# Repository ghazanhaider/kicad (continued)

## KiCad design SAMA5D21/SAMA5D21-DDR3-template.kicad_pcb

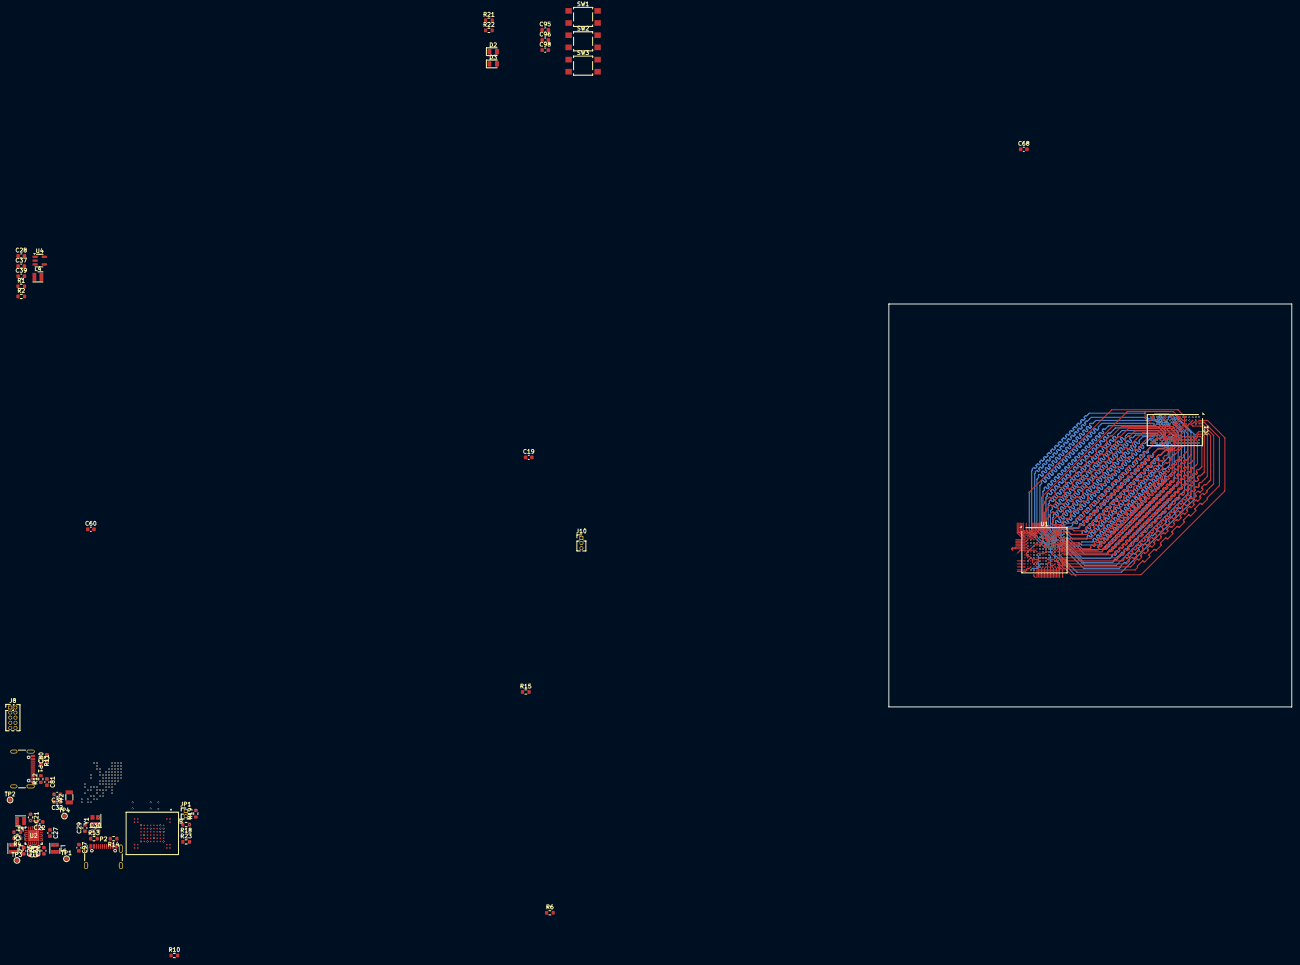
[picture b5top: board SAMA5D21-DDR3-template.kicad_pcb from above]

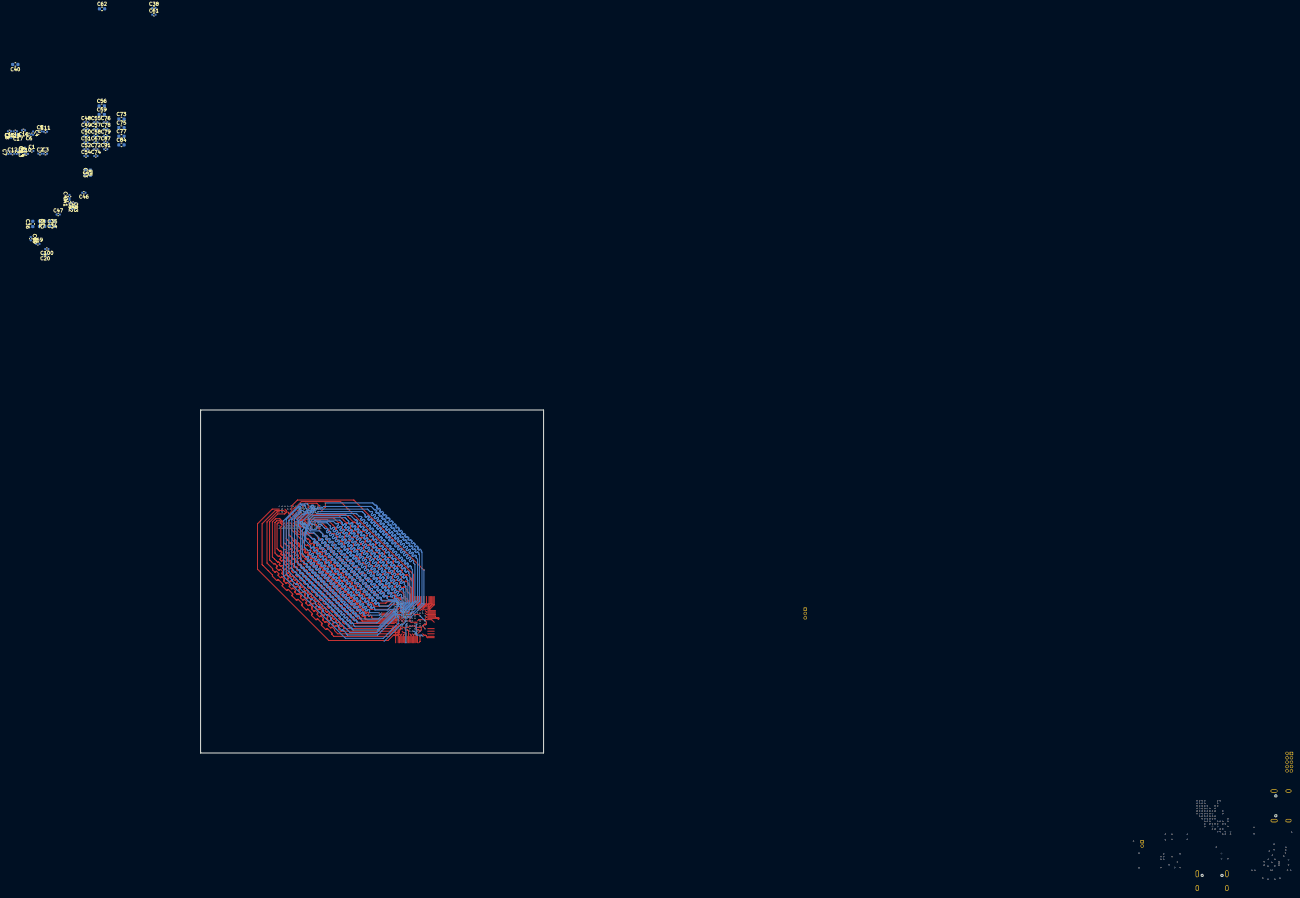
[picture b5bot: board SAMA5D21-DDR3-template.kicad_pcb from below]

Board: 4 copper layers, 127 parts (63 on the bottom side), 104 nets.

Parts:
C1, C2, C3, C4, C5, C6, C7, C8, C9, C10, C11, C12, C13, C14, C15, C16, C17, C18, C20, C38, C41, C42, C43, C44, C45, C46, C47, C48, C49, C50, C51, C52, C54, C55, C57, C58, C61, C67, C69, C72, C74, C76, C78, C79, C87, C91, C99, C100: 100nF; C_0402_1005Metric
C19, C37, C56, C59, C62, C68, C73, C75, C77, C84: 1uF; C_0603_1608Metric
C21, C23, C24: 22uF; C_0603_1608Metric
C22, C25, C26, C27, C28, C36, C39, C80, C81, C97: 4.7uF; C_0603_1608Metric
C29, C30, C31, C32: 16pF; C_0603_1608Metric
C33: 22pF; C_0603_1608Metric
C34, C35, C40, C95, C96, C98: 100nF; C_0603_1608Metric
C60: 10nF; C_0603_1608Metric
D2: LED; LED_0805_2012Metric
D3: PWR; LED_0805_2012Metric
IC1: D1216ECMDXGJD-U; Micron_FBGA-96_7.5x13.5mm_Layout9x16_P0.8mm
J8: SWD; PinHeader_2x05_P1.27mm_Vertical
J10: UART0; PinHeader_1x03_P1.27mm_Vertical
JP1: BOOT; PinHeader_1x02_P1.27mm_Vertical
L1, L2, L3: 2.2uH; L_Wurth_WE-LQSH-2512
L4: 10uH; L_Wurth_WE-LQSH-2512
P1: USB_PWR; USB_C_Receptacle_GCT_USB4105-xx-A_16P_TopMnt_Horizontal
P2: USB-B; USB_C_Receptacle_GCT_USB4105-xx-A_16P_TopMnt_Horizontal
R1: 92.82k; R_0603_1608Metric
R2: 5.1; R_0603_1608Metric
R3, R4, R6: 100k; R_0603_1608Metric
R5: 23.2k 1%; R_0603_1608Metric
R7, R8: 6.8k 1%; R_0603_1608Metric
R10: 240R 1%; R_0603_1608Metric
R11, R12: 5.1k 1%; R_0603_1608Metric
R13, R14: 56k 1%; R_0603_1608Metric
R15: 5.62k 1%; R_0603_1608Metric
R18, R19: 470k; R_0603_1608Metric
R21, R22, R23: 1k; R_0603_1608Metric
SW1: BUTTON; SW_SPST_TL3305A
SW2: START; SW_SPST_TL3305A
SW3: RESET; SW_SPST_TL3305A
TP1: VBUS; TestPoint_Pad_D1.0mm
TP2: 3.3V; TestPoint_Pad_D1.0mm
TP3: 1.35V; TestPoint_Pad_D1.0mm
TP4: 1.25V; TestPoint_Pad_D1.0mm
U1: ATSAMA5D21; Microchip_TFBGA-196_11x11mm_Layout14x14_P0.75mm_SMD
U2: PMIC; VQFN24_RMB_MCH
U3: MT29F4G08ABAFAH4-IT:F; BGA63C80P10X12_1050X1300X100N
U4: AP3012; SOT-23-5
Y1: 12MHz; Crystal_SMD_2520-4Pin_2.5x2.0mm
Y2: 32.768kHz; Crystal_SMD_3215-2Pin_3.2x1.5mm

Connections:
+1V25: C24.2, C38.2, C48.1, C49.1, C50.1, C51.1, C52.1, C62.2, C72.1, C73.1, C84.1, L3.1, TP4.1, U1.E8 (VDDCORE), U1.G8 (VDDCORE), U1.H8 (VDDCORE), U1.H9 (VDDCORE), U1.J5 (VDDCORE), U1.M7 (VDDUTMIC), U1.P3 (VDDPLLA), U2.13 (OUT3)
+1V35: C1.2, C2.2, C3.2, C4.2, C5.2, C6.2, C7.2, C8.2, C9.2, C10.2, C11.2, C12.2, C13.2, C14.2, C15.2, C16.2, C17.2, C18.2, C19.2, C23.1, C35.2, C36.1, C41.1, C42.1, C43.1, C44.1, C45.1, C46.1, C47.1, C60.1, C68.1, IC1.A1 (VDDQ_1), IC1.A8 (VDDQ_2), IC1.B2 (VDD_1), IC1.C1 (VDDQ_3), IC1.C9 (VDDQ_4), IC1.D2 (VDDQ_5), IC1.D9 (VDD_2), IC1.E9 (VDDQ_6), IC1.F1 (VDDQ_7), IC1.G7 (VDD_3), IC1.H2 (VDDQ_8), IC1.H9 (VDDQ_9), IC1.K2 (VDD_4), IC1.K8 (VDD_5), IC1.N1 (VDD_6), IC1.N9 (VDD_7), IC1.R1 (VDD_8), IC1.R9 (VDD_9), L2.1, R6.2, R8.1, TP3.1, U1.C6 (VDDIODDR), U1.E10 (VDDIODDR), U1.E12 (VDDIODDR), U1.G10 (VDDIODDR), U1.G12 (VDDIODDR), U1.H11 (VDDIODDR), U1.J10 (VDDIODDR), U2.6 (OUT2)
/DDR3/A0: IC1.N3 (A0), U1.E11 (DDR_A0)
/DDR3/A1: IC1.P7 (A1), U1.C11 (DDR_A1)
/DDR3/A2: IC1.P3 (A2), U1.B12 (DDR_A2)
/DDR3/A3: IC1.N2 (A3), U1.A12 (DDR_A3)
/DDR3/A4: IC1.P8 (A4), U1.D11 (DDR_A4)
/DDR3/A5: IC1.P2 (A5), U1.D14 (DDR_A5)
/DDR3/A6: IC1.R8 (A6), U1.B14 (DDR_A6)
/DDR3/A7: IC1.R2 (A7), U1.D9 (DDR_A7)
/DDR3/A8: IC1.T8 (A8), U1.C10 (DDR_A8)
/DDR3/A9: IC1.R3 (A9), U1.D10 (DDR_A9)
/DDR3/A10/AP: IC1.L7 (A10/AP), U1.F9 (DDR_A10)
/DDR3/A11: IC1.R7 (A11), U1.A11 (DDR_A11)
/DDR3/A12/BC#: IC1.N7 (A12/BC#), U1.B11 (DDR_A12)
/DDR3/A13: IC1.T3 (A13), U1.E13 (DDR_A13)
/DDR3/BA0: IC1.M2 (BA0), U1.F13 (DDR_BA0)
/DDR3/BA1: IC1.N8 (BA1), U1.G13 (DDR_BA1)
/DDR3/BA2: IC1.M3 (BA2), U1.F14 (DDR_BA2)
/DDR3/CAS#: IC1.K3 (CAS#), U1.C13 (DDR_CAS)
/DDR3/CK: IC1.J7 (CK), U1.A13 (DDR_CLK)
/DDR3/CK#: IC1.K7 (CK#), U1.B13 (DDR_CLKN)
/DDR3/CKE: IC1.K9 (CKE), U1.E14 (DDR_CKE)
/DDR3/CS#: IC1.L2 (CS#), U1.F11 (DDR_CS)
/DDR3/DDR_VREF: C34.2, C35.1, C40.1, IC1.H1 (VREFDQ), IC1.M8 (VREFCA), R7.1, R8.2, U1.C12 (DDR_VREF), U1.H12 (DDR_VREF)
/DDR3/DML: IC1.E7 (DML), U1.D8 (DDR_DQM0)
/DDR3/DMU: IC1.D3 (DMU), U1.G14 (DDR_DQM1)
/DDR3/DQL0: IC1.E3 (DQL0), U1.A9 (DDR_D4)
/DDR3/DQL1: IC1.F7 (DQL1), U1.B9 (DDR_D3)
/DDR3/DQL2: IC1.F2 (DQL2), U1.C8 (DDR_D2)
/DDR3/DQL3: IC1.F8 (DQL3), U1.C9 (DDR_D5)
/DDR3/DQL4: IC1.H3 (DQL4), U1.B7 (DDR_D0)
/DDR3/DQL5: IC1.H8 (DQL5), U1.B10 (DDR_D7)
/DDR3/DQL6: IC1.G2 (DQL6), U1.A7 (DDR_D1)
/DDR3/DQL7: IC1.H7 (DQL7), U1.A10 (DDR_D6)
/DDR3/DQSL: IC1.F3 (DQSL), U1.B8 (DDR_DQS0)
/DDR3/DQSL#: IC1.G3 (DQSL#), U1.A8 (DDR_DQSN0)
/DDR3/DQSU: IC1.C7 (DQSU), U1.K14 (DDR_DQS1)
/DDR3/DQSU#: IC1.B7 (DQSU#), U1.K13 (DDR_DQSN1)
/DDR3/DQU0: IC1.D7 (DQU0), U1.H13 (DDR_D8)
/DDR3/DQU1: IC1.C3 (DQU1), U1.L13 (DDR_D12)
/DDR3/DQU2: IC1.C8 (DQU2), U1.H14 (DDR_D9)
/DDR3/DQU3: IC1.C2 (DQU3), U1.L14 (DDR_D13)
/DDR3/DQU4: IC1.A7 (DQU4), U1.J14 (DDR_D11)
/DDR3/DQU5: IC1.A2 (DQU5), U1.K12 (DDR_D15)
/DDR3/DQU6: IC1.B8 (DQU6), U1.J13 (DDR_D10)
/DDR3/DQU7: IC1.A3 (DQU7), U1.J12 (DDR_D14)
/DDR3/RAS#: IC1.J3 (RAS#), U1.C14 (DDR_RAS)
/DDR3/WE#: IC1.L3 (WE#), U1.A14 (DDR_WE)
/DDR3/~DDR_RESET: IC1.T2 (RESET#), R6.1, U1.D13 (~DDR_RESET)
/NAND/NAND_CE: JP1.2 (B), R19.1, U3.C6 (CE#)
/Power/SHDN: U1.N1 (SHDN), U2.3 (PWRHLD)
/Power/START: C95.1, SW2.2, U2.14 (nSTRT)
/Power/WKUP: R4.1, U1.P1 (WKUP), U2.5 (nSTRTO)
/USB/VBG: R15.2, U1.L7 (VBG)
GNDADIOPLL: C1.1, C2.1, C3.1, C4.1, C5.1, C6.1, C7.1, C8.1, C9.1, C10.1, C11.1, C12.1, C13.1, C14.1, C15.1, C16.1, C17.1, C18.1, C19.1, C20.1, C21.2, C22.2, C23.2, C24.1, C25.2, C26.1, C27.2, C28.1, C29.1, C30.1, C31.2, C32.2, C33.2, C34.1, C36.2, C37.2, C38.1, C39.2, C40.2, C41.2, C42.2, C43.2, C44.2, C45.2, C46.2, C47.2, C48.2, C49.2, C50.2, C51.2, C52.2, C54.2, C55.2, C56.2, C57.2, C58.2, C59.2, C60.2, C61.1, C62.1, C67.1, C68.2, C69.1, C72.2, C73.2, C74.2, C75.2, C76.2, C77.2, C78.2, C79.2, C80.2, C81.2, C84.2, C87.2, C91.1, C95.2, C96.2, C97.2, C98.2, C99.1, C100.1, D3.1 (K), IC1.A9 (VSS_1), IC1.B1 (VSSQ_1), IC1.B3 (VSS_2), IC1.B9 (VSSQ_2), IC1.D1 (VSSQ_3), IC1.D8 (VSSQ_4), IC1.E1 (VSS_3), IC1.E2 (VSSQ_5), IC1.E8 (VSSQ_6), IC1.F9 (VSSQ_7), IC1.G1 (VSSQ_8), IC1.G8 (VSS_4), IC1.G9 (VSSQ_9), IC1.J2 (VSS_5), IC1.J8 (VSS_6), IC1.K1 (ODT), IC1.M1 (VSS_7), IC1.M9 (VSS_8), IC1.P1 (VSS_9), IC1.P9 (VSS_10), IC1.T1 (VSS_11), IC1.T9 (VSS_12), J8.3 (GND), J8.5 (GND), J8.9 (GNDDetect), J10.1, P1.A1 (GND), P1.A12 (GND), P1.B1 (GND), P1.B12 (GND), P1.S1 (SHIELD), P2.A1 (GND), P2.A12 (GND), P2.B1 (GND), P2.B12 (GND), P2.S1 (SHIELD), R2.2, R5.1, R7.2, R10.2, R11.1, R12.1, R15.1, SW1.1, SW2.1, SW3.1, U1.C7 (GNDIODDR), U1.D12 (GNDIODDR), U1.E4 (GNDIOP0), U1.E7 (GNDIOP0), U1.E9 (GNDIODDR), U1.F8 (GNDCORE), U1.F12 (GNDIODDR), U1.G7 (GNDCORE), U1.G9 (GNDCORE), U1.G11 (GNDIODDR), U1.H7 (GNDCORE), U1.H10 (GNDIODDR), U1.J2 (GNDANA), U1.J4 (GNDCORE), U1.J6 (GNDAUDIOPLL), U1.J11 (GNDIODDR), U1.K4 (GNDANA), U1.K9 (GNDIOP1), U1.K11 (VDDFUSE), U1.L6 (GNDDPLL), U1.L8 (GNDUTMII), U1.L12 (GNDIOP1), U1.M5 (GNDBU), U1.M8 (GNDUTMIC), U1.N6 (GNDOSC), U1.P4 (GNDPLLA), U2.4 (LPM), U2.9 (PGND2), U2.10 (PGND3), U2.16 (SGND), U2.22 (PGND1), U2.25 (GND), U3.C5 (VSS), U3.F7 (VSS), U3.K3 (VSS), U3.K8 (VSS), U4.2 (GND), Y1.2, Y1.4
JTAG_TCK: J8.4 (SWCLK/TCK), U1.G6 (PD14)
JTAG_TDI: J8.8 (TX/TDI), U1.H5 (PD15)
JTAG_TDO: J8.6 (SWO/TDO), U1.G1 (PD16)
JTAG_TMS: J8.2 (SWDIO/TMS), U1.G2 (PD17)
LCDPWM: U1.K10 (PC3), U4.4 (~EN)
NANDALE: U1.A6 (PB0), U3.C4 (ALE)
NANDCLE: U1.A5 (PB1), U3.D5 (CLE)
NANDCS3: JP1.1 (A), U1.M12 (PA31)
NANDOE: U1.B6 (PB2), U3.D4 (RE#)
NANDRDY: R23.1, U1.J9 (PC8), U3.C8 (R/B#)
NANDWE: U1.N12 (PA30), U3.C7 (WE#)
NAND_D0: U1.P9 (PA22), U3.H4 (I/O0)
NAND_D1: U1.P10 (PA23), U3.J4 (I/O1)
NAND_D2: U1.N10 (PA24), U3.K4 (I/O2)
NAND_D3: U1.L10 (PA25), U3.K5 (I/O3)
NAND_D4: U1.P11 (PA26), U3.K6 (I/O4)
NAND_D5: U1.P12 (PA27), U3.J7 (I/O5)
NAND_D6: U1.M11 (PA28), U3.K7 (I/O6)
NAND_D7: U1.N11 (PA29), U3.J8 (I/O7)
NRST: C96.1, J8.10 (~RESET), R3.1, SW3.2, U1.N3 (~RST), U2.2 (nRSTO)
unnamed: L4.1, U4.1 (SW)
unnamed: C37.1, R1.1
unnamed: D2.2 (A), R21.2
unnamed: D3.2 (A), R22.2
unnamed: IC1.L8 (ZQ), R10.1
unnamed: P1.A5 (CC1), R11.2
unnamed: P1.B5 (CC2), R12.2
unnamed: P2.A5 (CC1), R13.2
unnamed: P2.B5 (CC2), R14.2
unnamed: C33.1, R5.2, U1.F10 (DDR_CAL)
unnamed: P1.A7 (D-), P1.B7 (D-), U1.P7 (HHSDMA)
unnamed: P2.A7 (D-), P2.B7 (D-), U1.P8 (HHSDMB)
unnamed: P1.A6 (D+), P1.B6 (D+), U1.N7 (HHSDPA)
unnamed: P2.A6 (D+), P2.B6 (D+), U1.N8 (HHSDPB)
unnamed: C32.1, U1.M1 (XIN32), Y2.2
unnamed: C31.1, U1.L1 (XOUT32), Y2.1
unnamed: C29.2, U1.P5 (XIN), Y1.3
unnamed: C30.2, U1.P6 (XOUT), Y1.1
unnamed: L1.1, U2.23 (SW1)
unnamed: L2.2, U2.8 (SW2)
unnamed: L3.2, U2.11 (SW3)
unnamed: R18.2, U3.C3 (WP#)
unnamed: R1.2, R2.1, U4.3 (FB)
UART4-RX: J10.3, U1.B5 (PB3)
UART4-TX: J10.2, U1.A4 (PB4)
USER_BUTTON: C98.1, SW1.2, U1.L9 (PA18)
VBUS: C22.1, C25.1, C26.2, C27.1, C28.2, C80.1, C81.1, C97.1, L4.2, P1.A4 (VBUS), P1.A9 (VBUS), P1.B4 (VBUS), P1.B9 (VBUS), P2.A4 (VBUS), P2.A9 (VBUS), P2.B4 (VBUS), P2.B9 (VBUS), R13.1, R14.1, TP1.1, U2.7 (PVIN2), U2.12 (PVIN3), U2.15 (SELV3), U2.17 (VIN), U2.24 (PVIN1), U4.5 (IN)
VDDSDMMC: C20.2, C21.1, C39.1, C54.1, C55.1, C56.1, C57.1, C58.1, C59.1, C61.2, C67.2, C69.2, C74.1, C75.1, C76.1, C77.1, C78.1, C79.1, C87.1, C91.2, C99.2, C100.2, J8.1 (VTref), L1.2, R3.2, R4.2, R18.1, R19.2, R21.1, R22.1, R23.2, TP2.1, U1.D7 (VDDIOP0), U1.F4 (VDDIOP0), U1.H2 (VDDANA), U1.K3 (VDDANA), U1.K6 (VDDAUDIOPLL), U1.K7 (VDDUTMII), U1.K8 (VDDIOP1), U1.L2 (ADVREF), U1.L11 (VDDIOP1), U1.M4 (VDDBU), U1.N5 (VDDOSC), U2.1 (OUT1), U3.D3 (VCC), U3.G4 (VCC), U3.H8 (VCC), U3.J6 (VCC)
